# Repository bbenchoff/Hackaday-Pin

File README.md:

# Hackaday Pin

This is the repo for [the Hackaday blinky pin](https://hackaday.io/project/161358-hackaday-blinky-led-badge), and contains all the files necessary to order a few thousand more.

Instructions to assemble the badge are provided in the Hackaday.io link above.

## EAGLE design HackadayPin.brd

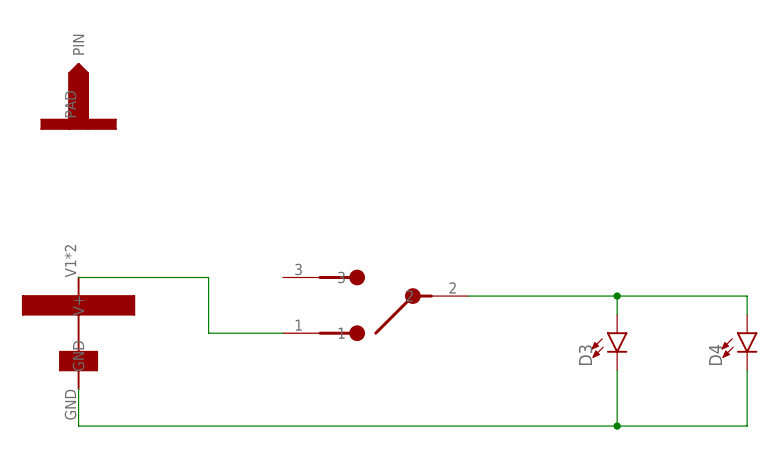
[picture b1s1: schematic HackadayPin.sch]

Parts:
D3, D4: LED5MM; LED_5MM
U$1: 1220BATTERY; BK-916
U$2: ALPSSLIDESW; SWITCH-SSSS810701
U$3: LAPELPIN

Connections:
GND1: D3.K (C), D4.K (C), U$1.GND
VBATT: U$1.V1 (V+), U$1.V2 (V+), U$2.1
VCC1: D3.A, D4.A, U$2.2

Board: 2 copper layers, 5 parts (3 on the bottom side), 3 nets, no tracks yet.

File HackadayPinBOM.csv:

Qty,Value,Device,Package,Parts,Description
2,,LED5MM,LED_5MM,"D3, D4",Chanzon 5mm RGB LED Slow Flash Low Profile
1,1220BATTERY,1220BATTERY,BK-916,U$1,1220 3V Lithium Battery
1,ALPSSLIDESW,ALPSSLIDESW,SWITCH-SSSS810701,U$2,Alps SSSS810701 or equivalent
1,LAPELPIN,LAPELPIN,LAPELPIN,U$3,Butterfly clutch pin back https://www.aliexpress.com/item/32801251429.html
1,Bag,Bag,,,8x12cm self-sealing plastic jewelry bag https://www.aliexpress.com/item/32801522148.html

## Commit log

2019-06-26 Initial commit
    My girlfriend says I can't commit who's laughing now
2019-08-27 Added BOM, fixed things
2019-08-27 fixed readme
2019-08-27 added gerbers

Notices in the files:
parts and their libraries:
SparkFun-LED: Licensing: Creative Commons ShareAlike 4.0 International - https://creativecommons.org/licenses/by-sa/4.0
